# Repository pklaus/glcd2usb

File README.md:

### This is a fork of Till Harbaum's glcd2usb

It adds a small tool which sets the brightness of the backlight
to zero and exits. This is helpful if you want to be able to shut
the display down and save power while having it still connected
to the computer as the brightness setting is preserved when the
tool exits.

Compiling:

    cd ./testclient
    make

Usage:

    ./dimdown

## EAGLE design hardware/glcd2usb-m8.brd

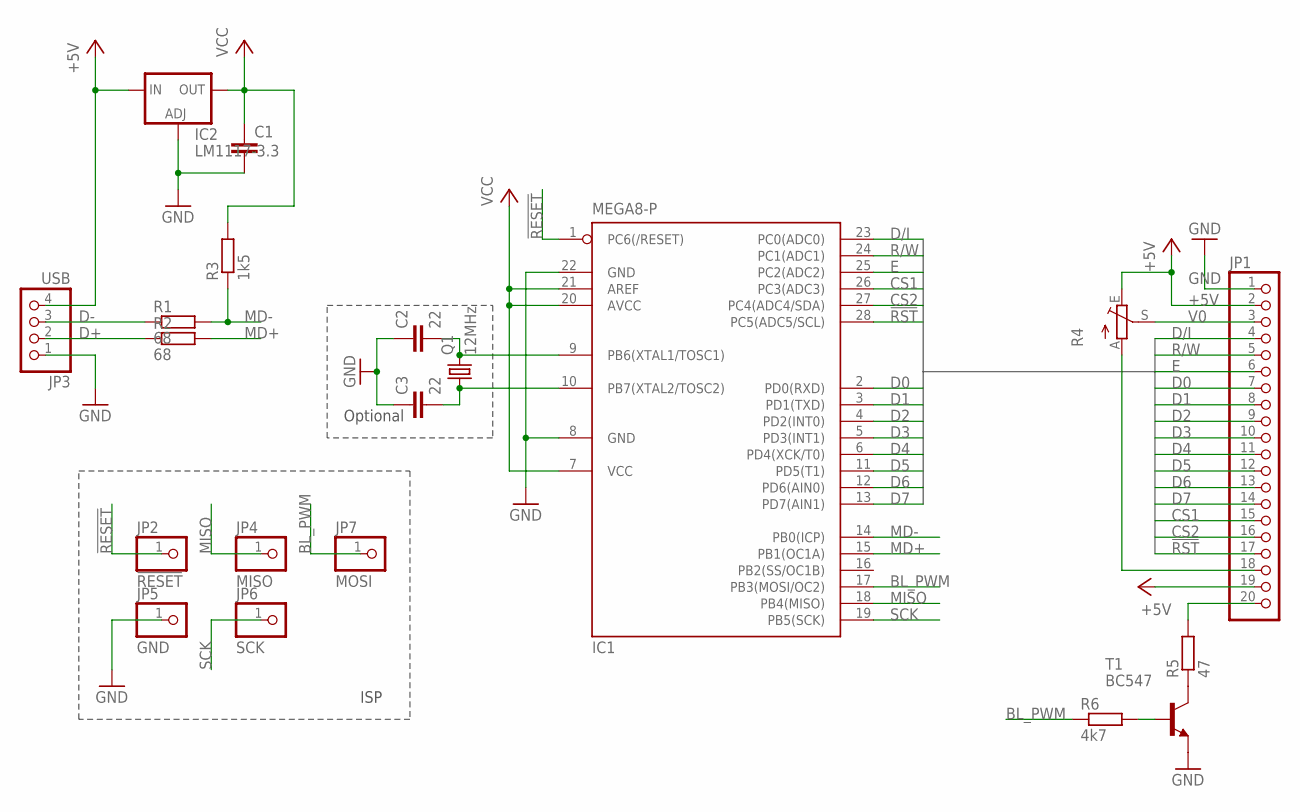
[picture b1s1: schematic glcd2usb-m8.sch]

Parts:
C1: C-EUC0603; C0603
C2, C3: 22; C0603
IC1: MEGA8-P; DIL28-3
IC2: LM1117-3.3; SOT223
JP1: PINHD-1X20; 1X20
JP2: !RESET; 1X01
JP3: USB; 1X04
JP4: MISO; 1X01
JP5: GND; 1X01
JP6: SCK; 1X01
JP7: MOSI; 1X01
Q1: 12MHz; HC49/S
R1, R2: 68; 0207/2V
R3: 1k5; 0207/2V
R4: TRIM_EU-B25P; B25P
R5: 47; 0204V
R6: 4k7; 0207/2V
T1: BC547; TO92

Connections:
!RESET: IC1.1 (PC6(/RESET)), JP2.1
!RST: IC1.28 (PC5(ADC5/SCL)), JP1.17
+5V: IC2.3 (IN), JP1.2, JP1.19, JP3.4, R4.E
BL_PWM: IC1.17 (PB3(MOSI/OC2)), JP7.1, R6.1
CS1: IC1.26 (PC3(ADC3)), JP1.15
CS2: IC1.27 (PC4(ADC4/SDA)), JP1.16
D0: IC1.2 (PD0(RXD)), JP1.7
D1: IC1.3 (PD1(TXD)), JP1.8
D2: IC1.4 (PD2(INT0)), JP1.9
D3: IC1.5 (PD3(INT1)), JP1.10
D4: IC1.6 (PD4(XCK/T0)), JP1.11
D5: IC1.11 (PD5(T1)), JP1.12
D6: IC1.12 (PD6(AIN0)), JP1.13
D7: IC1.13 (PD7(AIN1)), JP1.14
D+: JP3.2, R2.1
D-: JP3.3, R1.1
D/I: IC1.23 (PC0(ADC0)), JP1.4
E: IC1.25 (PC2(ADC2)), JP1.6
GND: C1.2, C2.1, C3.1, IC1.8 (GND), IC1.22 (GND), IC2.1 (ADJ), JP1.1, JP3.1, JP5.1, T1.1 (E)
MD+: IC1.15 (PB1(OC1A)), R2.2
MD-: IC1.14 (PB0(ICP)), R1.2, R3.1
MISO: IC1.18 (PB4(MISO)), JP4.1
unnamed: R5.1, T1.3 (C)
unnamed: JP1.20, R5.2
unnamed: C3.2, IC1.10 (PB7(XTAL2/TOSC2)), Q1.1
unnamed: R6.2, T1.2 (B)
unnamed: C2.2, IC1.9 (PB6(XTAL1/TOSC1)), Q1.2
unnamed: JP1.18, R4.A
R/W: IC1.24 (PC1(ADC1)), JP1.5
SCK: IC1.19 (PB5(SCK)), JP6.1
V0: JP1.3, R4.S
VCC: C1.1, IC1.7 (VCC), IC1.20 (AVCC), IC1.21 (AREF), IC2.4 (OUT), R3.2

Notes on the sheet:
ISP
Optional

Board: 2 copper layers, 20 parts (1 on the bottom side), 32 nets, no tracks yet.

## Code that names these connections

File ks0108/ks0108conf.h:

/*! \file ks0108conf.h \brief Graphic LCD driver configuration. */
//*****************************************************************************
//
// File Name	: 'ks0108conf.h'
// Title		: Graphic LCD driver for HD61202/KS0108 displays
// Author		: Pascal Stang - Copyright (C) 2001-2003
// Date			: 10/19/2001
// Revised		: 5/1/2003
// Version		: 0.5
// Target MCU	: Atmel AVR
// Editor Tabs	: 4
//
// NOTE: This code is currently below version 1.0, and therefore is considered
// to be lacking in some functionality or documentation, or may not be fully
// tested.  Nonetheless, you can expect most functions to work.
//
// This code is distributed under the GNU Public License
//		which can be found at http://www.gnu.org/licenses/gpl.txt
//
//*****************************************************************************


#ifndef KS0108CONF_H
#define KS0108CONF_H

// GLCD_PORT_INTERFACE specifics
// make sure these parameters are not already defined elsewhere
#define GLCD_CTRL_PORT	PORTC	// PORT for LCD control signals
#define GLCD_CTRL_DDR	DDRC	// DDR register of LCD_CTRL_PORT
#define GLCD_CTRL_RS	PC0	// pin for LCD Register Select
#define GLCD_CTRL_RW	PC1	// pin for LCD Read/Write
#define GLCD_CTRL_E	PC2	// pin for LCD Enable
#define GLCD_CTRL_CS0	PC3	// pin for LCD Controller 0 Chip Select
#define GLCD_CTRL_CS1	PC4	// pin for LCD Controller 1 Chip Select(*)
#define GLCD_CTRL_RESET	PC5	// pin for LCD Reset
// (*) NOTE: additonal controller chip selects are optional and 
// will be automatically used per each step in 64 pixels of display size
// Example: Display with 128 hozizontal pixels uses 2 controllers
#define GLCD_DATA_PORT	PORTD	// PORT for LCD data signals
#define GLCD_DATA_DDR	DDRD	// DDR register of LCD_DATA_PORT
#define GLCD_DATA_PIN	PIND	// PIN register of LCD_DATA_PORT

// LCD geometry defines (change these definitions to adapt code/settings)
#define GLCD_XPIXELS	128		// pixel width of entire display
#define GLCD_YPIXELS	64		// pixel height of entire display
#define GLCD_CONTROLLER_XPIXELS	64	// pixel width of one display controller

// Set text size of display
// These definitions are not currently used and will probably move to glcd.h
#define GLCD_TEXT_LINES           8     // visible lines
#define GLCD_TEXT_LINE_LENGTH    22     // internal line length

#endif

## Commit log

2013-05-27 import glcd2usb 2011-05-06
2013-05-27 update v-usb
2013-05-27 add .gitignore
2013-05-27 fix progmem
2013-05-27 add make F_CPU=x
2013-05-27 gc all unused funcs/data
2013-05-27 add schematic for m8 sersion (for breadboard)
2013-05-27 Revert "add schematic for m8 sersion (for breadboard)"
    This reverts commit 8eb2687e423933f2a8d9d092e601b87ec3de2260.
2013-05-27 use PortC for contntrol (glcd lib limitations)
2013-05-27 configure glcd lib
2013-05-28 add usb osccal, osctune; fix ports, timers
2013-05-29 fix connections
2013-05-29 fix v-usb, ports. alpha
2013-06-24 add readme for github
2014-03-21 also .gitignore the testclient binary
2014-03-21 New utility tool to set the backlight to 0
2014-03-21 README added for dimdown tool
